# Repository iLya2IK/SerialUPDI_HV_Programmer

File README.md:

# SerialUPDI_HV_Programmer

Простой программатор UPDI с функцией запуска протокола UPDI высоковольтным импульсом 12V. Последовательность сигналов для такого программирования приведена в разделе любого даташита к avr. Например:
[33.3.2.2 UPDI Enable with 12V Override of RESET pin](https://ww1.microchip.com/downloads/en/DeviceDoc/40001912A.pdf)

Инициализация протокола UPDI за счет подачи импульса высокого напряжения (12V) на пин UPDI/RESET предназначена для разблокировки устройства (в основном, типа Attiny), для которого данный пин был ранее запрограммирован на ввод-вывод и более не реагирует на программаторы другого типа (без импульса высокого напряжения).

Устройство разработано на основе схемы [SerialUPDI HV Programmer based on CH340E and MT360](https://github.com/wagiminator/AVR-Programmer/blob/master/SerialUPDI_HV_Programmer). Основные отличия:
1. Используется понижающий преобразователь напряжения NCP1529A для снижения напряжения от 5 В до 3.3 В
2. Вместо переключателя флажкового типа используется простая перемычка
3. Разъем USB поверхностного монтажа переделан в разъем типа JST XH2.54
4. В целях упрощения ручной пайки используются более крупные SMD компоненты форм-фактора 1206 для емкостей и 0805 для резисторов

Устройство собрано и протестировано. Для программирования использовал утилиту [Pure-C utility for programming AVR devices with UPDI interface using a standard TTL serial port](https://github.com/Polarisru/updiprog). Удалось записать hex файл, выставить/сбросить фьюзы с заблокированным пином UPDI.

# References and copyrights
* [ATtiny214/414/814. Datasheet Preliminary](https://ww1.microchip.com/downloads/en/DeviceDoc/40001912A.pdf)
* [SerialUPDI HV Programmer based on CH340E and MT360](https://github.com/wagiminator/AVR-Programmer/blob/master/SerialUPDI_HV_Programmer)
* [Pure-C utility for programming AVR devices with UPDI interface using a standard TTL serial port](https://github.com/iLya2IK/updiprog)
* Copyright (c) 2023, Ilya Medvedkov

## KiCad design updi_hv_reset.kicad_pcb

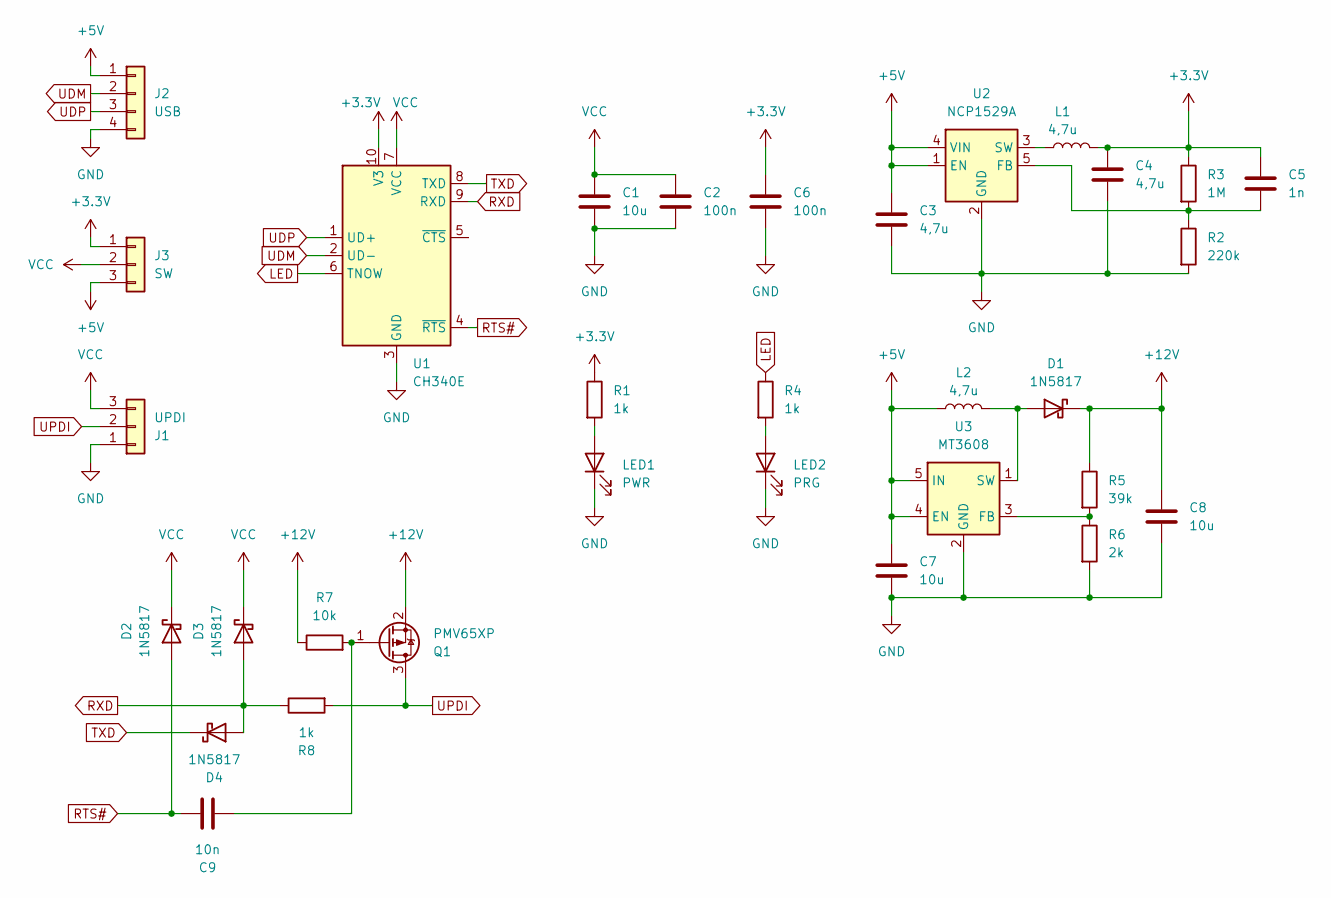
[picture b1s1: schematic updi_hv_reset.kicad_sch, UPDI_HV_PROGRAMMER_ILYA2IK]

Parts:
C1, C7, C8: 10u; C_1206_3216Metric
C2, C6: 100n; C_1206_3216Metric
C3, C4: 4,7u; C_1206_3216Metric
C5: 1n; C_1206_3216Metric
C9: 10n; C_1206_3216Metric
D1, D2, D3, D4: 1N5817; D_SMA
J1: UPDI; PinHeader_1x03_P2.54mm_Vertical
J2: USB; JST_XH_B4B-XH-A_1x04_P2.50mm_Vertical
J3: SW; PinHeader_1x03_P2.54mm_Vertical
L1, L2: 4,7u; L_1206_3216Metric
LED1: PWR; LED_0805_2012Metric
LED2: PRG; LED_0805_2012Metric
Q1: PMV65XP; SOT-23
R1, R4, R8: 1k; R_0805_2012Metric
R2: 220k; R_0805_2012Metric
R3: 1M; R_0805_2012Metric
R5: 39k; R_0805_2012Metric
R6: 2k; R_0805_2012Metric
R7: 10k; R_0805_2012Metric
U1: CH340E; MSOP-10_3x3mm_P0.5mm
U2: NCP1529A; SOT-23-5
U3: MT3608; SOT-23-6

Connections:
+3.3V: C4.1, C5.1, C6.1, J3.1, L1.2, R1.1, R3.1, U1.10 (V3)
+5V: C3.1, C7.1, J2.1, J3.3, L2.1, U2.1 (EN), U2.4 (VIN), U3.4 (EN), U3.5 (IN)
+12V: C8.1, D1.1 (K), Q1.2 (S), R5.1, R7.1
GND: C1.2, C2.2, C3.2, C4.2, C6.2, C7.2, C8.2, J1.1, J2.4, LED1.1 (K), LED2.1 (K), R2.2, R6.2, U1.3 (GND), U2.2 (GND), U3.2 (GND)
LED: R4.1, U1.6 (TNOW)
unnamed: D1.2 (A), L2.2, U3.1 (SW)
unnamed: LED1.2 (A), R1.2
unnamed: LED2.2 (A), R4.2
unnamed: C9.2, Q1.1 (G), R7.2
unnamed: C5.2, R2.1, R3.2, U2.5 (FB)
unnamed: L1.1, U2.3 (SW)
unnamed: R5.2, R6.1, U3.3 (FB)
RTS#: C9.1, D2.2 (A), U1.4 (~RTS)
RXD: D3.2 (A), D4.2 (A), R8.1, U1.9 (RXD)
TXD: D4.1 (K), U1.8 (TXD)
UDM: J2.2, U1.2 (UD-)
UDP: J2.3, U1.1 (UD+)
UPDI: J1.2, Q1.3 (D), R8.2
VCC: C1.1, C2.1, D2.1 (K), D3.1 (K), J1.3, J3.2, U1.7 (VCC)

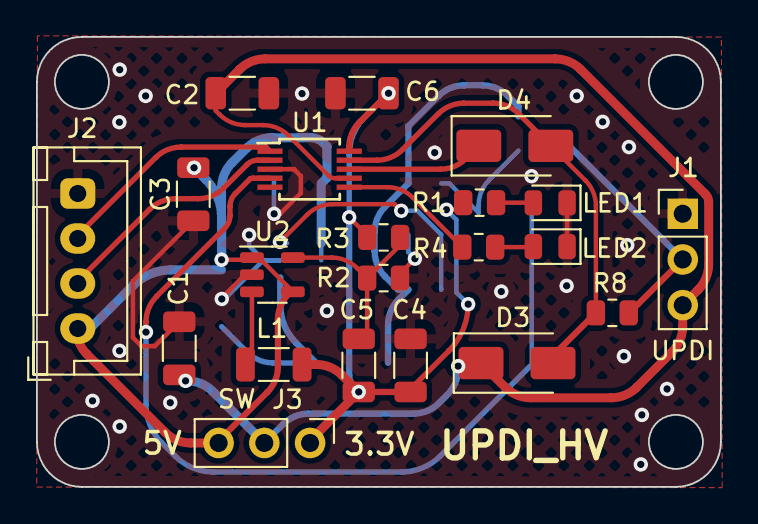
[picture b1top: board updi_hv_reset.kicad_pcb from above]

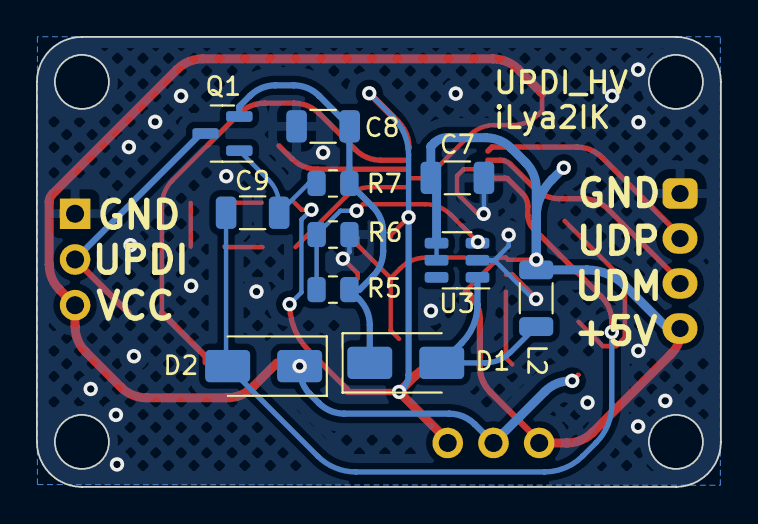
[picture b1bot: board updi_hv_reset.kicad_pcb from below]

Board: 2 copper layers, 38.0 x 25.0 mm, 32 parts (11 on the bottom side), 19 nets.

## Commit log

2023-10-12 README and pics added
2023-10-12 pics edited
2023-10-12 schematic pic added
2023-10-24 box design files added
2023-10-24 gcode removed
2024-04-18 updiprog link changed to iLya2IK fork
